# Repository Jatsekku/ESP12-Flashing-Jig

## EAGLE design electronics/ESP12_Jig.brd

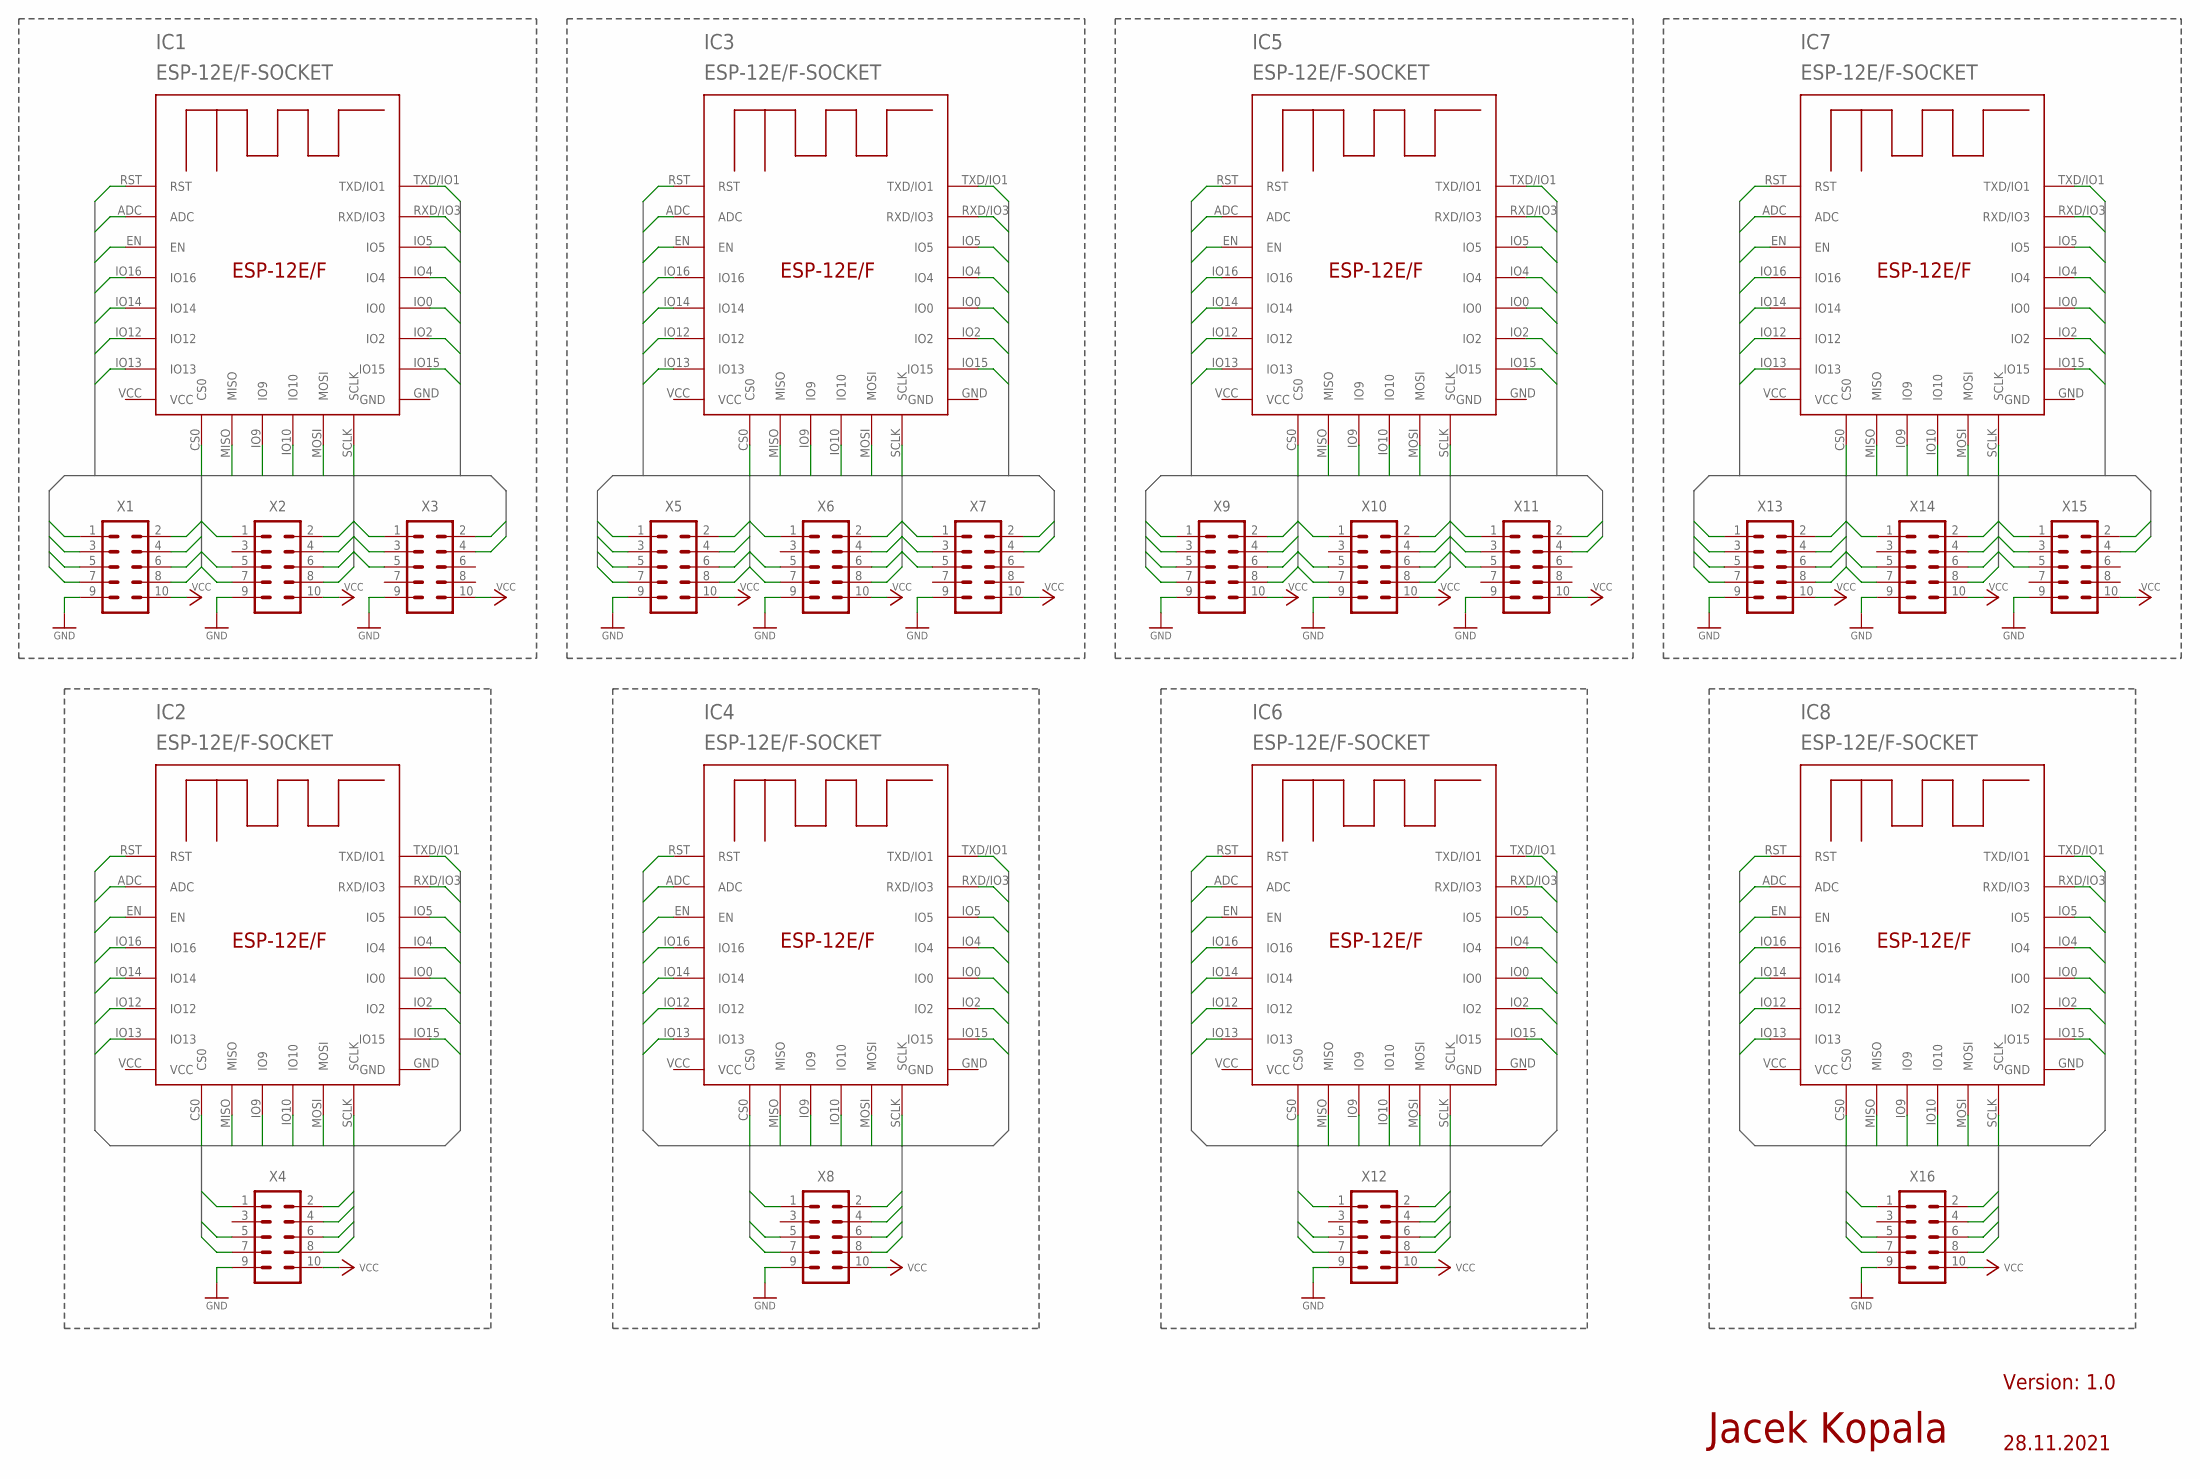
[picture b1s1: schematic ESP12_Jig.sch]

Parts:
IC1, IC2, IC3, IC4, IC5, IC6, IC7, IC8: ESP-12E/F-SOCKET
X1, X2, X3, X4, X5, X6, X7, X8, X9, X10, X11, X12, X13, X14, X15, X16: ML10

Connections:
ADC_1: IC1.ADC, X1.8
ADC_3: IC3.ADC, X5.8
ADC_4: IC7.ADC, X13.8
ADC_5: IC5.ADC, X9.8
ADC_6: IC2.ADC
ADC_7: IC6.ADC
ADC_8: IC8.ADC
ADC_9: IC4.ADC
CS0_1: IC1.CS0, X1.2
CS0_3: IC3.CS0, X5.2
CS0_4: IC7.CS0, X13.2
CS0_5: IC5.CS0, X9.2
CS0_6: IC2.CS0
CS0_7: IC6.CS0
CS0_8: IC8.CS0
CS0_9: IC4.CS0
EN_1: IC1.EN, X2.5
EN_3: IC3.EN, X6.5
EN_4: IC7.EN, X14.5
EN_5: IC5.EN, X10.5
EN_6: IC2.EN, X4.5
EN_7: IC6.EN, X12.5
EN_8: IC8.EN, X16.5
EN_9: IC4.EN, X8.5
G0_1: IC1.IO0, X2.4
G0_3: IC3.IO0, X6.4
G0_4: IC7.IO0, X14.4
G0_5: IC5.IO0, X10.4
G0_6: IC2.IO0, X4.4
G0_7: IC6.IO0, X12.4
G0_8: IC8.IO0, X16.4
G0_9: IC4.IO0, X8.4
G2_1: IC1.IO2, X2.2
G2_3: IC3.IO2, X6.2
G2_4: IC7.IO2, X14.2
G2_5: IC5.IO2, X10.2
G2_6: IC2.IO2, X4.2
G2_7: IC6.IO2, X12.2
G2_8: IC8.IO2, X16.2
G2_9: IC4.IO2, X8.2
G4_1: IC1.IO4, X3.4
G4_3: IC3.IO4, X7.4
G4_4: IC7.IO4, X15.4
G4_5: IC5.IO4, X11.4
G4_6: IC2.IO4
G4_7: IC6.IO4
G4_8: IC8.IO4
G4_9: IC4.IO4
G5_1: IC1.IO5, X3.5
G5_3: IC3.IO5, X7.5
G5_4: IC7.IO5, X15.5
G5_5: IC5.IO5, X11.5
G5_6: IC2.IO5
G5_7: IC6.IO5
G5_8: IC8.IO5
G5_9: IC4.IO5
G9_1: IC1.IO9, X1.1
G9_3: IC3.IO9, X5.1
G9_4: IC7.IO9, X13.1
G9_5: IC5.IO9, X9.1
G9_6: IC2.IO9
G9_7: IC6.IO9
G9_8: IC8.IO9
G9_9: IC4.IO9
G10_1: IC1.IO10, X3.2
G10_3: IC3.IO10, X7.2
G10_4: IC7.IO10, X15.2
G10_5: IC5.IO10, X11.2
G10_6: IC2.IO10
G10_7: IC6.IO10
G10_8: IC8.IO10
G10_9: IC4.IO10
G12_1: IC1.IO12, X1.5
G12_3: IC3.IO12, X5.5
G12_4: IC7.IO12, X13.5
G12_5: IC5.IO12, X9.5
G12_6: IC2.IO12
G12_7: IC6.IO12
G12_8: IC8.IO12
G12_9: IC4.IO12
G13_1: IC1.IO13, X1.4
G13_3: IC3.IO13, X5.4
G13_4: IC7.IO13, X13.4
G13_5: IC5.IO13, X9.4
G13_6: IC2.IO13
G13_7: IC6.IO13
G13_8: IC8.IO13
G13_9: IC4.IO13
G14_1: IC1.IO14, X1.6
G14_3: IC3.IO14, X5.6
G14_4: IC7.IO14, X13.6
G14_5: IC5.IO14, X9.6
G14_6: IC2.IO14
G14_7: IC6.IO14
G14_8: IC8.IO14
G14_9: IC4.IO14
G15_1: IC1.IO15, X2.1
G15_3: IC3.IO15, X6.1
G15_4: IC7.IO15, X14.1
G15_5: IC5.IO15, X10.1
G15_6: IC2.IO15, X4.1
G15_7: IC6.IO15, X12.1
G15_8: IC8.IO15, X16.1
G15_9: IC4.IO15, X8.1
G16_1: IC1.IO16, X1.7
G16_3: IC3.IO16, X5.7
G16_4: IC7.IO16, X13.7
G16_5: IC5.IO16, X9.7
G16_6: IC2.IO16
G16_7: IC6.IO16
G16_8: IC8.IO16
G16_9: IC4.IO16
GND: IC1.GND, IC2.GND, IC3.GND, IC4.GND, IC5.GND, IC6.GND, IC7.GND, IC8.GND, X1.9, X2.9, X3.9, X4.9, X5.9, X6.9, X7.9, X8.9, X9.9, X10.9, X11.9, X12.9, X13.9, X14.9, X15.9, X16.9
MISO_1: IC1.MISO, X1.3
MISO_3: IC3.MISO, X5.3
MISO_4: IC7.MISO, X13.3
MISO_5: IC5.MISO, X9.3
MISO_6: IC2.MISO
MISO_7: IC6.MISO
MISO_8: IC8.MISO
MISO_9: IC4.MISO
MOSI_1: IC1.MOSI, X3.3
MOSI_3: IC3.MOSI, X7.3
MOSI_4: IC7.MOSI, X15.3
MOSI_5: IC5.MOSI, X11.3
MOSI_6: IC2.MOSI
MOSI_7: IC6.MOSI
MOSI_8: IC8.MOSI
MOSI_9: IC4.MOSI
RST_1: IC1.RST, X2.7
RST_3: IC3.RST, X6.7
RST_4: IC7.RST, X14.7
RST_5: IC5.RST, X10.7
RST_6: IC2.RST, X4.7
RST_7: IC6.RST, X12.7
RST_8: IC8.RST, X16.7
RST_9: IC4.RST, X8.7
RXD_1: IC1.RXD/IO3, X2.6
RXD_3: IC3.RXD/IO3, X6.6
RXD_4: IC7.RXD/IO3, X14.6
RXD_5: IC5.RXD/IO3, X10.6
RXD_6: IC2.RXD/IO3, X4.6
RXD_7: IC6.RXD/IO3, X12.6
RXD_8: IC8.RXD/IO3, X16.6
RXD_9: IC4.RXD/IO3, X8.6
SCLK_1: IC1.SCLK, X3.1
SCLK_3: IC3.SCLK, X7.1
SCLK_4: IC7.SCLK, X15.1
SCLK_5: IC5.SCLK, X11.1
SCLK_6: IC2.SCLK
SCLK_7: IC6.SCLK
SCLK_8: IC8.SCLK
SCLK_9: IC4.SCLK
TXD_1: IC1.TXD/IO1, X2.8
TXD_3: IC3.TXD/IO1, X6.8
TXD_4: IC7.TXD/IO1, X14.8
TXD_5: IC5.TXD/IO1, X10.8
TXD_6: IC2.TXD/IO1, X4.8
TXD_7: IC6.TXD/IO1, X12.8
TXD_8: IC8.TXD/IO1, X16.8
TXD_9: IC4.TXD/IO1, X8.8
VCC: IC1.VCC, IC2.VCC, IC3.VCC, IC4.VCC, IC5.VCC, IC6.VCC, IC7.VCC, IC8.VCC, X1.10, X2.10, X3.10, X4.10, X5.10, X6.10, X7.10, X8.10, X9.10, X10.10, X11.10, X12.10, X13.10, X14.10, X15.10, X16.10

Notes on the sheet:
Version: 1.0
Jacek Kopala
28.11.2021

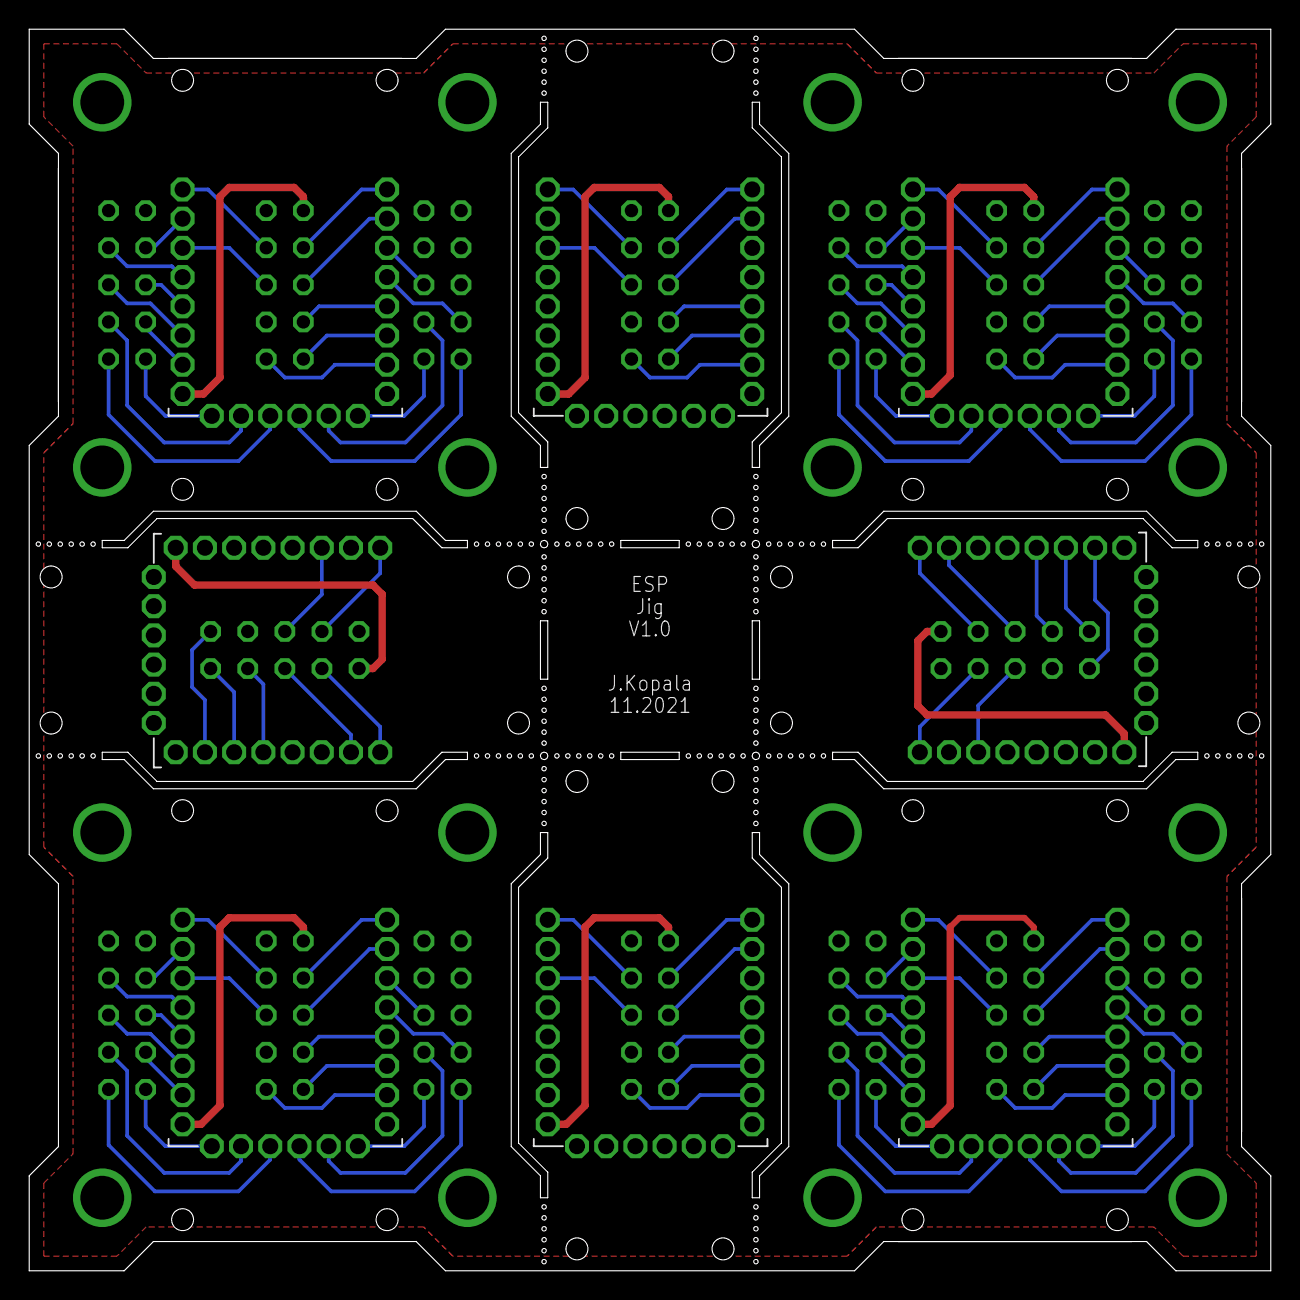
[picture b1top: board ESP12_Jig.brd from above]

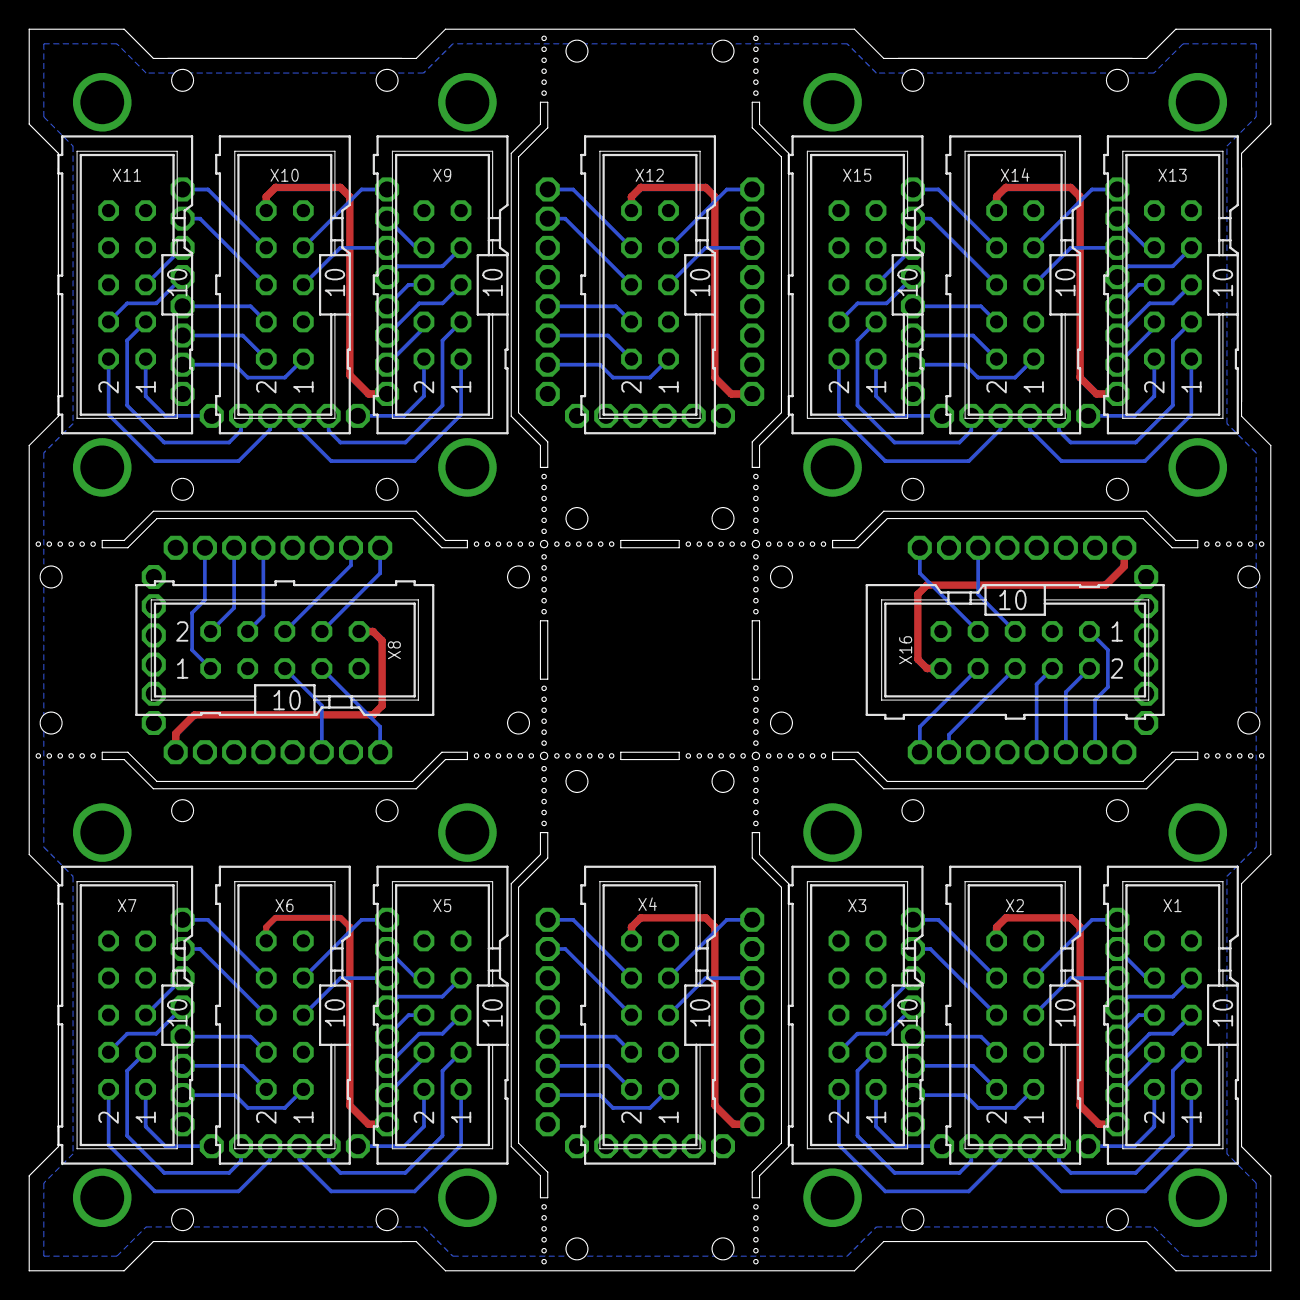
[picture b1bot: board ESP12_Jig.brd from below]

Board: 2 copper layers, 85.0 x 85.0 mm, 24 parts (16 on the bottom side), 110 nets.

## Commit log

2022-08-29 [electronics] Add schematic and PCB design.
    This commit contains:
    - Schematic in Eagle: ESP12_Jig.sch
    - Schematic in PDF: ESP12_Jig_sch.pdf
    - PCB layout in Eagle: ESP12_Jig.brd
    - PCB view in PNG: ESP12_Jig_view_bot/top.png
